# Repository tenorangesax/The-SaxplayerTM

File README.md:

# The-Saxplayer™
The Saxplayer™ is a device that houses a ESP32E for the microcontroller, a OLED display to see what songs are playing, 3 MX-Style keyboard switches for navigation of songs, a rotary encoder switch for adjusting the volume and navigating menus, a micro sd card slot for storing your music, and a audio jack for headphones or output to speakers! Also has a cool case I made along with it!

**FIRMWARE GUIDE AT BOTTOM!**

**[WORKING VIDEO DEMO LINK!!!](https://youtu.be/1pTQ9vNJp9s)**

**FINAL SHOTS:**

**THE CASE:**

**3D VIEWER:**

**THE SCHEMATIC:**

**PCB EDITOR:**

**CASE MODELING:**

**BOM:**

| Item name | Quantity | Single price | Link to purchase | Description |
|---|---:|---:|---|---|
| Cherry MX-compatible PCB switch | 3 | $0.40 | [MechanicalKeyboards](https://mechanicalkeyboards.com/products/cherry-mx-honey-silent-45g-tactile-pcb-mount-switch) | Keyboard switch for the 3 keys |
| Micro SD card socket | 1 | $1.52 | PCBA assembled by JLCPCB | MicroSD push-push SMT socket |
| 1.3in 128x64 I2C OLED display | 1 | $5.27 | [Amazon](https://www.amazon.com/JAMHER-Display-Self-Luminous-Projects-Raspberry/dp/B0F3D2ZQZ4?th=1) | Monochrome OLED display |
| 10k resistor | 4 | $0.02 | [Amazon](https://www.amazon.com/LuminologyPro-1000-Piece-Resistor-25-Value-1%CE%A9-1M%CE%A9/dp/B0F4P352BB) | Through-hole resistor |
| 3.5mm audio jack | 1 | $1.52 | [DigiKey](https://www.digikey.com/en/products/detail/same-sky-formerly-cui-devices/SJ2-35954A-SMT-TR/6619576) | Right-angle SMT audio jack |
| 10uF capacitor | 1 | $0.10 | [Amazon](https://www.amazon.com/Rubycon-Electrolytic-Capacitor-Aluminum-Capacitors/dp/B0F8C24M5R?s=industrial&th=1) | Polarized capacitor |
| Rotary encoder with push switch | 1 | $4.90 | [Amazon](https://www.amazon.com/WWZMDiB-Encoder-Digital-Potentiometer-Arduino/dp/B0C6Q67V97?s=industrial) | Rotary input control |
| 0.1uF capacitor | 2 | $0.05 | [Amazon](https://www.amazon.com/BOJACK-Capacitor-Multilayer-Monolithic-Assortment/dp/B085RDTCCV?th=1) | Decoupling capacitor |
| 10uF capacitor | 2 | $0.10 | [Amazon](https://www.amazon.com/BOJACK-Capacitor-Multilayer-Monolithic-Assortment/dp/B085RDTCCV?th=1) | Capacitor |
| 4.7k resistor | 2 | $0.02 | [Amazon](https://www.amazon.com/LuminologyPro-1000-Piece-Resistor-25-Value-1%CE%A9-1M%CE%A9/dp/B0F4P352BB) | Pull-up / signal resistor |
| ESP32 DevKitC board | 1 | $10.00 | [Amazon](https://www.amazon.com/HiLetgo-ESP-WROOM-32-Development-Microcontroller-Integrated/dp/B0718T232Z?s=industrial) | Main controller board |

# Saxplayer™ Firmware (MicroPython)

WAV music player firmware for the Saxplayer board (ESP32-WROOM, SH1106/SSD1306 OLED, microSD, 3 MX switches, EC11 encoder, 3.5mm jack driven by the ESP32's internal DACs).

## Flashing

1. Install [esptool](https://docs.micropython.org/en/latest/esp32/tutorial/intro.html) and grab the latest ESP32 MicroPython firmware from micropython.org/download/ESP32_GENERIC/
2. Flash it (adjust the port):
   ```
   esptool.py --chip esp32 --port /dev/tty.usbserial-XXXX erase_flash
   esptool.py --chip esp32 --port /dev/tty.usbserial-XXXX write_flash -z 0x1000 ESP32_GENERIC-*.bin
   ```
3. Copy this Firmware folder's `.py` files to the board with [mpremote](https://docs.micropython.org/en/latest/reference/mpremote.html):
   ```
   mpremote cp boot.py config.py inputs.py wavplayer.py main.py :
   mpremote mkdir lib
   mpremote cp lib/sh1106.py lib/ssd1306.py :lib/
   mpremote reset
   ```

## Preparing music

Convert anything (MP3, FLAC, ...) to player readable WAV with ffmpeg, then drop it on the SD card (FAT32):

```
ffmpeg -i song.mp3 -ac 1 -ar 16000 -sample_fmt s16 song.wav
```

Mono, 16 kHz, 16-bit is prefered.
## Controls

| Input | Browser | Now playing |
|---|---|---|
| SW1 (up) | move up | previous track |
| SW3 (down) | move down | next track |
| SW2 (select) | play | play / pause |
| Encoder turn | volume | volume |
| Encoder push | rescan SD | stop, back to browser |

## Files

- `config.py` — every pin assignment and tunable, matches the KiCad netlist
- `inputs.py` — IRQ-driven buttons + quadrature encoder decoding
- `wavplayer.py` — WAV parsing and DAC playback (viper-optimized conversion)
- `main.py` — SD mount, file browser, now-playing UI
- `lib/sh1106.py`, `lib/ssd1306.py` — OLED drivers (1.3" panels are usually SH1106; switch with `OLED_DRIVER` in config.py)

## Hardware errors (check before assembling!)

The rotary encoder's common pin (C) and switch return (S2) reach GND **only through capacitors C4/C5**. Capacitors block DC, so as designed the encoder can never actually pull GPIO13/14/27 low, so turns and pushes won't register.

It would already be bridged for you by me, but if not, bridge C4 and C5 with a solder blob/0Ω resistor.

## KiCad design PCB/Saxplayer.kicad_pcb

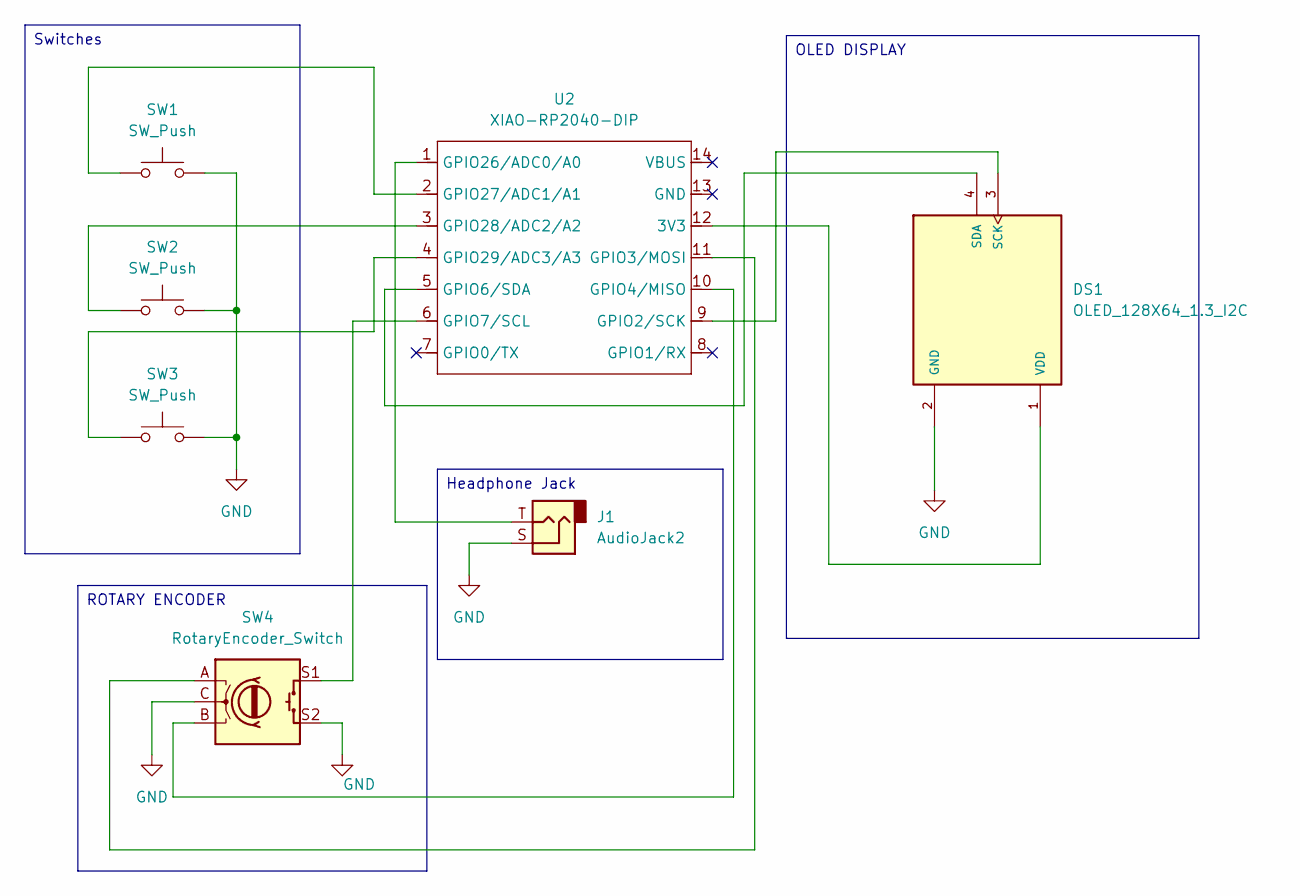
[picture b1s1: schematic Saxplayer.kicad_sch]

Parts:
DS1: OLED_128X64_1.3_I2C; LCD_OLED_128X64_1.3_I2C; PARTREV NA
J1: AudioJack2; Jack_3.5mm_CUI_SJ-3523-SMT_Horizontal
SW1, SW2, SW3: SW_Push; SW_Cherry_MX_1.00u_PCB
SW4: RotaryEncoder_Switch; RotaryEncoder_Alps_EC11E-Switch_Vertical_H20mm
U2: XIAO-RP2040-DIP; MCU_Seeed_ESP32C3

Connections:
GND: DS1.2 (GND), J1.S, SW1.2, SW2.2, SW3.2, SW4.C, SW4.S2
unnamed: DS1.3 (SCK), U2.9 (GPIO2/SCK)
unnamed: DS1.4 (SDA), U2.5 (GPIO6/SDA)
unnamed: DS1.1 (VDD), U2.12 (3V3)
unnamed: SW4.A, U2.11 (GPIO3/MOSI)
unnamed: SW4.B, U2.10 (GPIO4/MISO)
unnamed: SW4.S1, U2.6 (GPIO7/SCL)
unnamed: J1.T, U2.1 (GPIO26/ADC0/A0)
unnamed: SW1.1, U2.2 (GPIO27/ADC1/A1)
unnamed: SW2.1, U2.3 (GPIO28/ADC2/A2)
unnamed: SW3.1, U2.4 (GPIO29/ADC3/A3)

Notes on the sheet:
OLED DISPLAY
Switches
Headphone Jack
ROTARY ENCODER

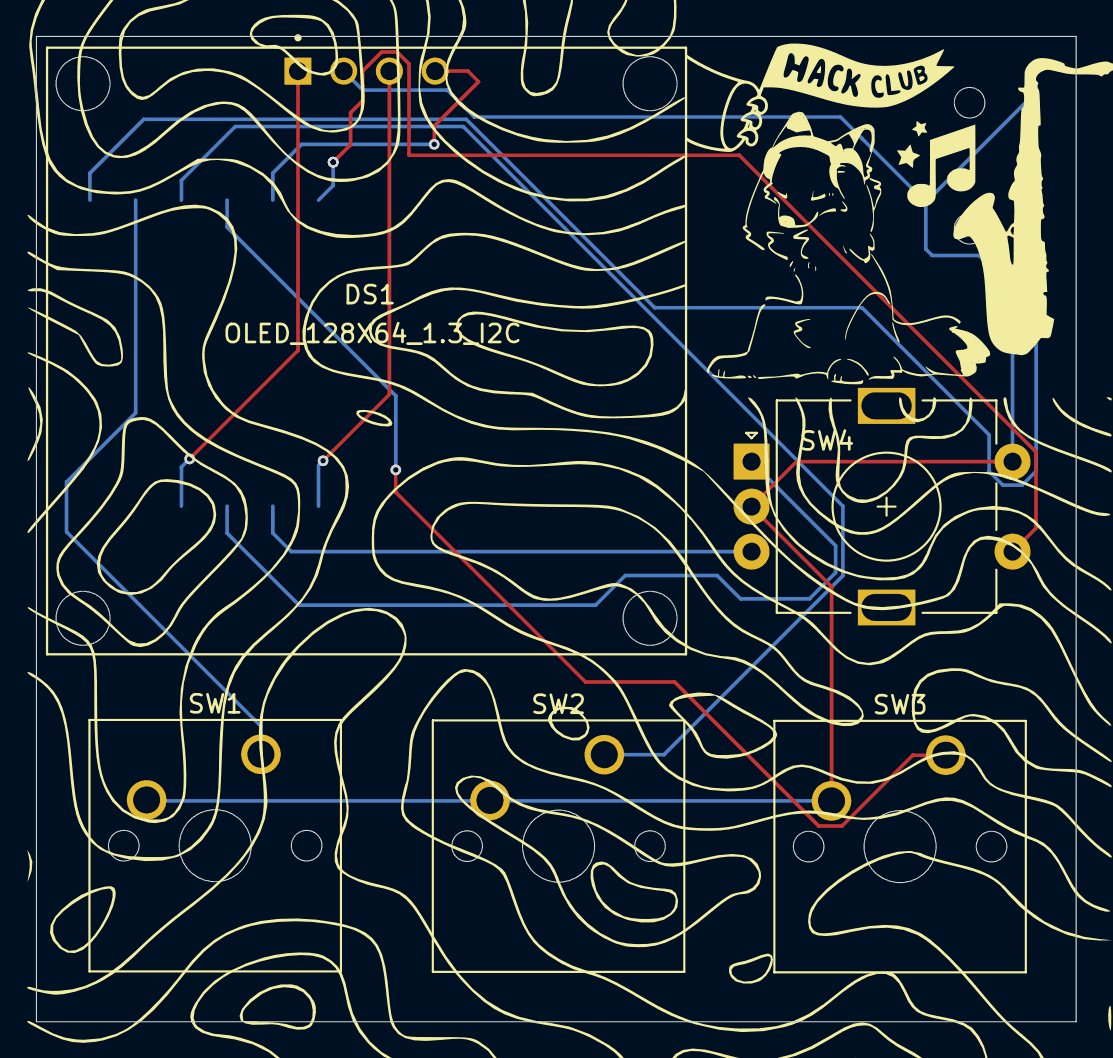
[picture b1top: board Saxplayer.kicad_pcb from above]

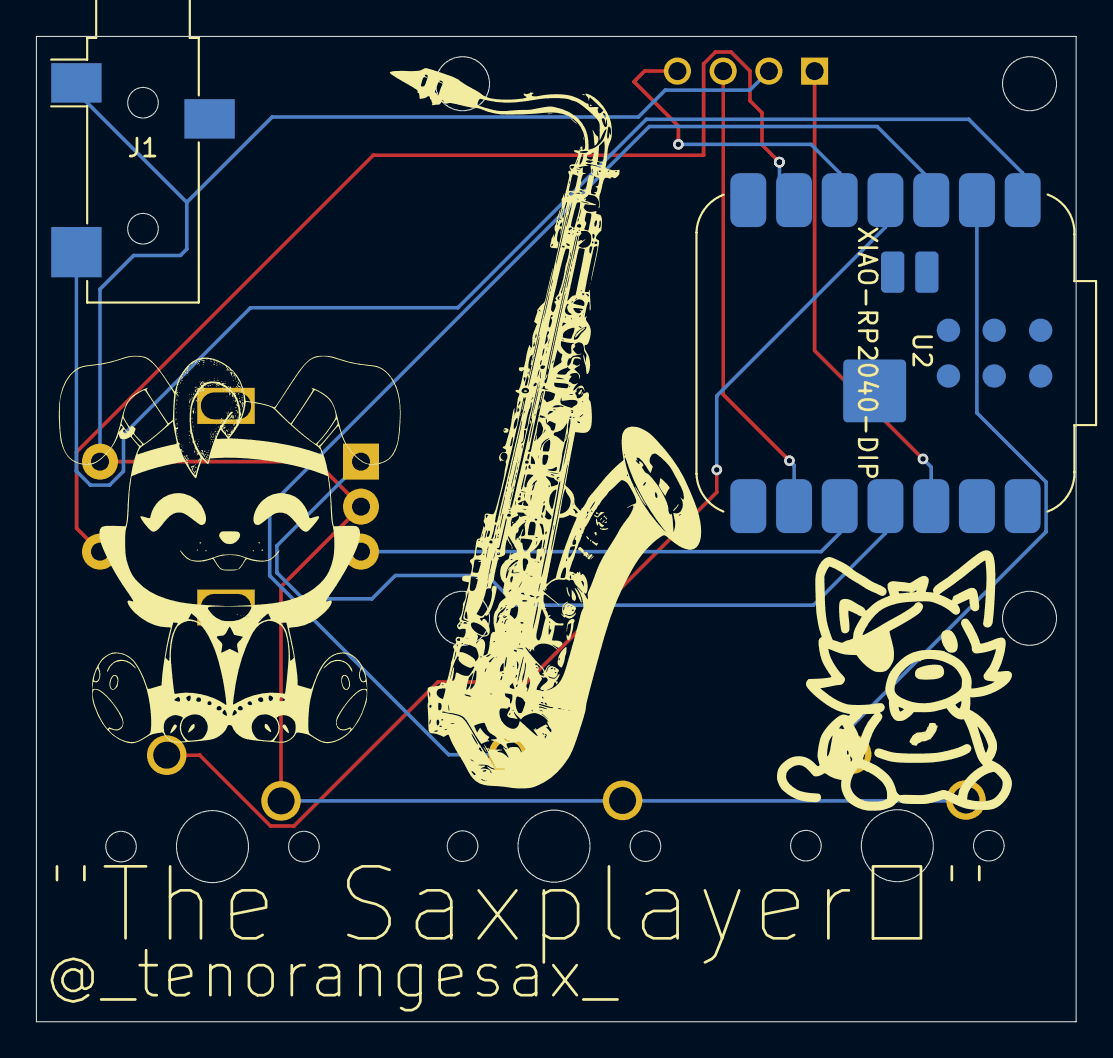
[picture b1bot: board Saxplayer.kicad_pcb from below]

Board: 2 copper layers, 57.8 x 54.7 mm, 7 parts (2 on the bottom side), 11 nets.

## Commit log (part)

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2026-03-27 Create sfd
2026-03-27 Create dgffhg
2026-03-27 Create fsd
2026-03-27 Create urtf
2026-03-27 Create fdasdfsafdas
2026-03-27 Create fdas
2026-03-30 Create jifsdfsdsdf
2026-03-30 Create sdf
2026-03-30 Create OLD
2026-03-30 Create sfdsdf
2026-03-30 Create sdffd
2026-04-18 Create jgfh
